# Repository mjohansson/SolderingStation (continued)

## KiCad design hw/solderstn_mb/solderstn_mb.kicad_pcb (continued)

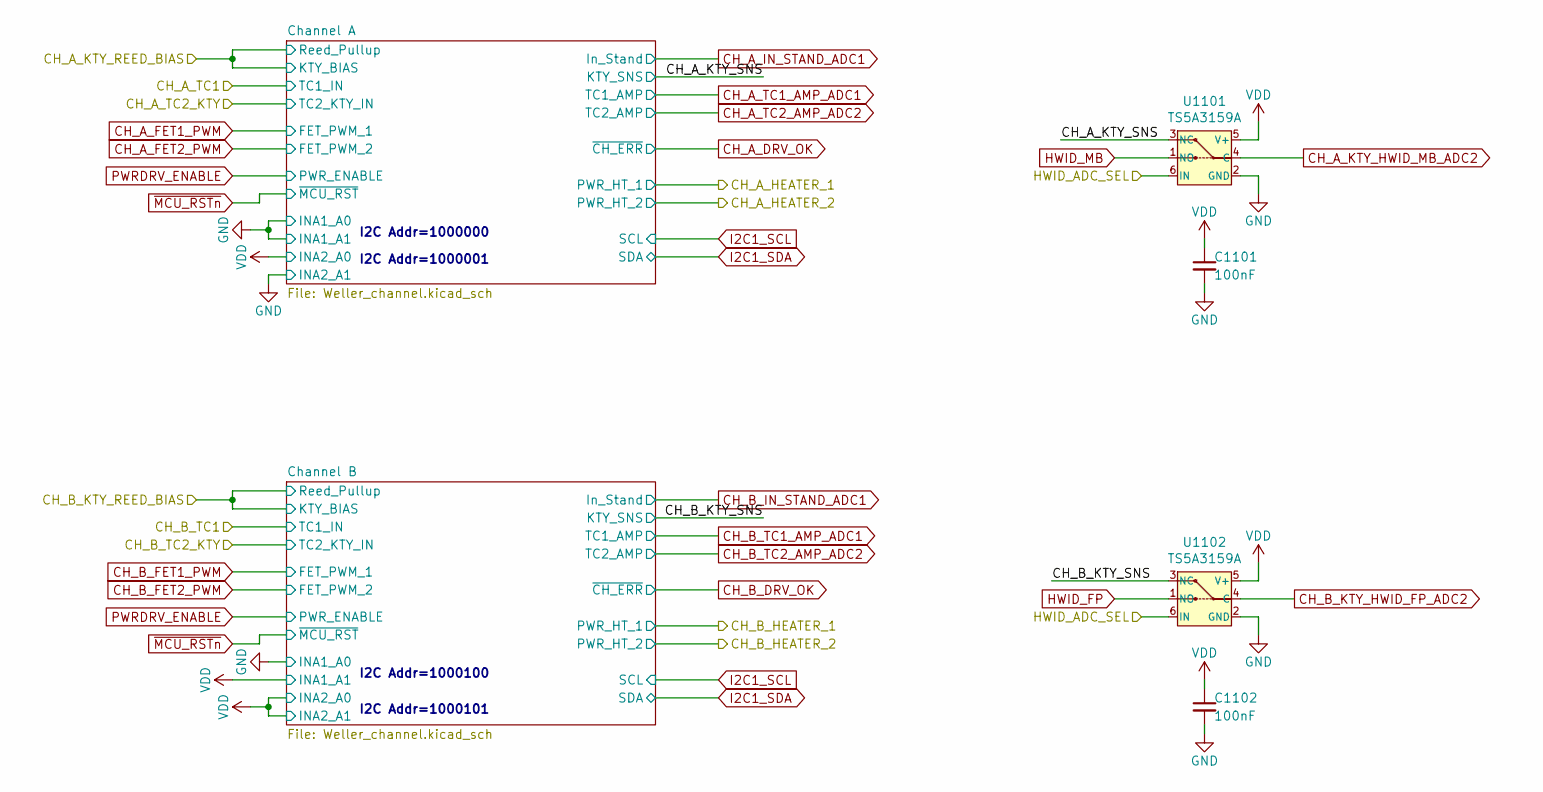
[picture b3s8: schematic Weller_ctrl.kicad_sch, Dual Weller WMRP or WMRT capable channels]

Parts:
C1101, C1102: 100nF; C_0402_1005Metric; JLC_part Basic
U1101, U1102: TS5A3159A; TSOT-23-6; JLC_part Extended

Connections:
/STM32F429 MCU/HWID_ADC_SELECT: U1101.6 (IN), U1102.6 (IN); also elsewhere on the board
/Weller contol/CH_A_KTY_SNS: U1101.3 (NC); also elsewhere on the board
/Weller contol/CH_B_KTY_SNS: U1102.3 (NC); also elsewhere on the board
AGND: C1101.2, C1102.2, U1101.2 (GND), U1102.2 (GND); also elsewhere on the board
CH_A_KTY_HWID_MB_ADC2: U1101.4 (C); also elsewhere on the board
CH_B_KTY_HWID_FP_ADC2: U1102.4 (C); also elsewhere on the board
HWID_FP: U1102.1 (NO); also elsewhere on the board
HWID_MB: U1101.1 (NO); also elsewhere on the board
VCC: C1101.1, C1102.1, U1101.5 (V+), U1102.5 (V+); also elsewhere on the board

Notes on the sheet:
I2C Addr=1000100
I2C Addr=1000001
I2C Addr=1000101
I2C Addr=1000000

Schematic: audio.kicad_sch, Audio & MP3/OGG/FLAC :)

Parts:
C1801, C1804, C1805, C1808: 2u2; C_0603_1608Metric; JLC_part Basic
C1802, C1806: 100nF; C_0402_1005Metric; JLC_part Basic
C1803, C1807: 470nF; C_0402_1005Metric; JLC_part Basic
J1801, J1803: CES-30207-158L120-67_Molex-PicoBlade_conn; Molex_PicoBlade_53398-0271_1x02-1MP_P1.25mm_Vertical
J1802, J1804: CES-703116-28PM_JST-conn; JST_PH_S2B-PH-SM4-TB_1x02-1MP_P2.00mm_Horizontal
JP1801, JP1802: dogbone_3_ud; db3_ud_0402
LS1801, LS1803: CES-30207-158L120-67; CUI_CES-30207
LS1802, LS1804: CES-703116-28PM; CUI_CES-703116-28PM
R1801, R1806: 15k; R_0402_1005Metric; JLC_part Basic
R1802, R1807: 1k5; R_0402_1005Metric; JLC_part Basic
R1803, R1809: 10k; R_0402_1005Metric; JLC_part Basic
R1804, R1810: 0R; R_1206_3216Metric; JLC_part Basic
R1805, R1808: DNM; R_0402_1005Metric
U1801, U1802: TS4990IDT; SOIC-8_3.9x4.9mm_P1.27mm

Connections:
/Audio & int. speakers/VLSI VS1063 DSP/codec/VS_L_out: C1807.2, R1808.1; also elsewhere on the board
/Audio & int. speakers/VLSI VS1063 DSP/codec/VS_R_out: C1803.2, R1805.2; also elsewhere on the board
/Rear panel connections/L_ch: U1802.8 (VOUT2); also elsewhere on the board
/Rear panel connections/L_int: R1810.1; also elsewhere on the board
/Rear panel connections/R_ch: U1801.8 (VOUT2); also elsewhere on the board
/Rear panel connections/R_int: R1804.1; also elsewhere on the board
AGND: C1801.1, C1802.1, C1804.1, C1805.1, C1806.1, C1808.1, R1805.1, R1808.2, U1801.7 (GND), U1802.7 (GND); also elsewhere on the board
unnamed: C1803.1, R1803.2
unnamed: C1804.2, U1801.2 (BYPASS), U1801.3 (Vin+)
unnamed: C1807.1, R1809.2
unnamed: C1808.2, U1802.2 (BYPASS), U1802.3 (Vin+)
unnamed: J1801.1 (+), J1802.1 (+), R1804.2
unnamed: J1801.2 (-), J1802.2 (-), R1802.1, U1801.5 (VOUT1)
unnamed: J1803.1 (+), J1804.1 (+), R1810.2
unnamed: J1803.2 (-), J1804.2 (-), R1807.1, U1802.5 (VOUT1)
unnamed: R1801.1, R1802.2
unnamed: R1801.2, R1803.1, U1801.4 (Vin-)
unnamed: R1806.1, R1807.2
unnamed: R1806.2, R1809.1, U1802.4 (Vin-)
VCC: JP1801.3, JP1802.3; also elsewhere on the board
VMAIN: C1801.2, C1802.2, C1805.2, C1806.2, JP1801.1, JP1801.2, JP1802.1, JP1802.2, U1801.6 (VCC), U1802.6 (VCC); also elsewhere on the board
~AUDIO_MUTEn: U1801.1 (~STBY), U1802.1 (~STBY); also elsewhere on the board

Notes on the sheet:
JST JST_PH_S2B-PH-SM4-TB for CES-703116
- +
F_AC [470n, 10k] = 34Hz
Using internal speakers until a 3.5mm plug is inserted; then switching to the external load. The switch is integrated in the headphone connector (rear panel)
A = Rf/Ri = 1,65 Vi = 3,0 * 1,65 -> Vo_max = 4,95
Right channel
Optional MP3/Ogg codec
Header for CES-30207 : Molex Picoblade 53398-0271
Left channel
Alternative interior enclosed speakers, CUI Devices CES-series; either 30x20x7mm or 70x31x16.5mm
Can encode MCU DAC-output to Ogg or MP3 (e.g. to record FM-radio data) Or decode MP3/Ogg/FLAC/etc compressed audio files, e.g. from USB storage or network streams
Molex Picoblade 53398-0271 for CES-30207

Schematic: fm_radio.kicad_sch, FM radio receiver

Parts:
C2201: 100nF; C_0402_1005Metric; JLC_part Basic
C2202: 10nF; C_0402_1005Metric; JLC_part Basic
C2203: 10pF; C_0402_1005Metric; JLC_part Basic
C2204: 470nF; C_0402_1005Metric; JLC_part Basic
C2205: 470pF; C_0402_1005Metric; JLC_part Basic
D2201, D2202: CM1213A-01SO; SOT-23
J801, J2204: alt-placement; SMA_Molex_73251-2200_Horizontal
J2201: Conn_01x02; PinHeader_1x02_P2.54mm_Vertical
J2202: Molex_PicoBlade-53398-0271; Molex_PicoBlade_53398-0271_1x02-1MP_P1.25mm_Vertical
J2203: Conn_Coaxial; SMA_Molex_73251-2200_Horizontal
JP2201: dogbone_3_ud; db3_ud_0402
JP2202, JP2203, JP2204: dogbone_2_ud; db2_ud_0402
L2201: 220nH; L_0603_1608Metric; JLC_part Extended
R2201: 560R; R_0603_1608Metric; JLC_part Basic
R2202, R2203: 1k; R_0402_1005Metric; JLC_part Basic
U2201: Si4735-D60-GU; SSOP-24_3.9x8.7mm_P0.635mm

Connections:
/FM-radio rx/FMI: C2205.1, D2202.1 (CH1), J2202.1, JP2203.1, JP2203.2, JP2204.1
AGND: C2201.2, C2203.1, D2201.2 (VP), D2201.3 (VN), D2202.2 (VP), D2202.3 (VN), J2201.2, J2202.2, J2203.2 (Ext), JP2201.1, JP2201.2, JP2202.1, JP2202.2, L2201.2, U2201.9 (RFGND), U2201.13 (GND), U2201.14 (GND), U2201.16 (~SEN); also elsewhere on the board
AVDD: C2202.1, U2201.21 (VA); also elsewhere on the board
FM_I2S_CK: R2203.1; also elsewhere on the board
FM_I2S_SD: R2201.1; also elsewhere on the board
FM_I2S_WS: C2203.2, R2202.1; also elsewhere on the board
I2C1_SCL: U2201.17 (SCLK); also elsewhere on the board
I2C1_SDA: U2201.18 (SDIO); also elsewhere on the board
unnamed: C2202.2, U2201.22 (DBYP)
unnamed: C2204.1, D2201.1 (CH1), J2201.1
unnamed: C2204.2, U2201.12 (AMI)
unnamed: C2205.2, L2201.1, U2201.8 (FMI)
unnamed: J2203.1 (In), JP2204.2
unnamed: R2201.2, U2201.1 (DOUT)
unnamed: R2202.2, U2201.2 (DFS)
unnamed: R2203.2, U2201.3 (GPO3/[DCLK])
RCLKo_8M: U2201.19 (RCLK); also elsewhere on the board
VCC: C2201.1, JP2201.3, U2201.20 (VD); also elsewhere on the board
~FM_INTn: U2201.4 (GPO2/[~INT]); also elsewhere on the board
~SYS_RSTn: U2201.15 (~RST); also elsewhere on the board

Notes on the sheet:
To ferrite loop stick, apprx 180-450µH
(was: 56nH / LQW18AN56NJ00D)
~{SEN} = 0 : I2C addr=0010001 ~{SEN} = 1 : I2C addr=1100011
(OTS cable assm: e.g. 151340203)
To e.g. 1/4 FM wire- or screw telescope (whip) antenna

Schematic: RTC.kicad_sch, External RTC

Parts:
C2101, C2102, C2103: 100nF; C_0402_1005Metric; JLC_part Basic
Q2101: AO3401A; SOT-23; JLC_part Basic
Q2102: DMG1013T; SOT-523_handsoldering; JLC_part Extended
R2102: 10k; R_0402_1005Metric; JLC_part Basic
RN2101: 4x10k_0402; R_Array_Convex_4x0402; JLC_part Basic
RTC2101: DS3231_Module_6pins; DS3231_module_6pin_horizontal_mnt
U2101: DS3231M; SOIC-16W_7.5x10.3mm_P1.27mm; JLC_part Basic
U2102: AT24C256C-SSHL-T; SO-8_3.9x4.9mm_P1.27mm; JLC_part Basic
U2103: DS3231MZ; SOIC-8_3.9x4.9mm_P1.27mm; JLC_part Extended

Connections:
+BATT: U2101.14 (VBAT), U2103.6 (VBAT)
/STM32F429 MCU/32kHz: RTC2101.1 (32K), U2101.1 (32KHZ), U2103.1 (32KHZ); also elsewhere on the board
/STM32F429 MCU/External RTC/PG: Q2101.1 (G), Q2102.1 (G), U2101.4 (~RST), U2103.4 (~RST)
/STM32F429 MCU/External RTC/~WEn: Q2101.3 (D), Q2102.3 (D), RN2101.5 (R4.2), U2102.7 (WP)
/STM32F429 MCU/~RTC_INTn: R2102.2, RTC2101.2 (~INT/SQW), U2101.3 (~INT/SQW), U2103.3 (~INT/SQW); also elsewhere on the board
AGND: C2101.1, C2102.1, C2103.1, RN2101.4 (R4.1), RTC2101.6 (GND), U2101.5 (GND), U2101.6 (GND), U2101.7 (GND), U2101.8 (GND), U2101.9 (GND), U2101.10 (GND), U2101.11 (GND), U2101.12 (GND), U2101.13 (GND), U2102.4 (GND), U2103.5 (GND); also elsewhere on the board
I2C1_SCL: RTC2101.3 (SCL), U2101.16 (SCL), U2102.6 (SCL), U2103.8 (SCL); also elsewhere on the board
I2C1_SDA: RTC2101.4 (SDA), U2101.15 (SDA), U2102.5 (SDA), U2103.7 (SDA); also elsewhere on the board
unnamed: RN2101.6 (R3.2), U2102.3 (A2)
unnamed: RN2101.7 (R2.2), U2102.2 (A1)
unnamed: RN2101.8 (R1.2), U2102.1 (A0)
VCC: C2101.2, C2102.2, C2103.2, Q2101.2 (S), Q2102.2 (S), R2102.1, RN2101.1 (R1.1), RN2101.2 (R2.1), RN2101.3 (R3.1), RTC2101.5 (VCC), U2101.2 (VCC), U2102.8 (VCC), U2103.2 (VCC); also elsewhere on the board

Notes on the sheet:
EEPROM write-protection on power-loss: ~{RES}/PG pin high when VDD > 2.7V(max), open-drain low when VDD < ~{2.5V(typ}). Do not pull-up, internal ~{50K} in DS3231.
DS3231 RTC module
Alt. fp : Mount either -M or -MZ Place SOIC-8 footprint overlapping the pins 1-4/13-16 of SOIC-16
TODO: Remove all on-board RTC & EEPROM, use just RTC-module
DS3132 I2C address : b1101000<R~{w}>
Alternative footprint : Mount Q2101 or Q2102 but not both. footprint SC-523 can be placed overlapping the SOT-23
EEPROM I2C address : b1010<A2..A0><R/~{w}> = b1010111<R~{w}>

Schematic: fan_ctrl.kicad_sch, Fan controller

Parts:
C601: 10uF/16V; C_0805_2012Metric; JLC_part Basic
C602: 100nF; C_0402_1005Metric; JLC_part Basic
JP601: dogbone_3_ud; db3_ud_0402
M601: Fan_4pin; FanPinHeader_1x04_P2.54mm_Vertical; Mfg_pn Molex 47053-1000
Q601: DMG1012T; SOT-523_handsoldering; JLC_part Extended
R601: 12k; R_0402_1005Metric; JLC_part Basic
R602, R603: 10k; R_0402_1005Metric; JLC_part Basic
U601: 74LVC2G17gw; SOT-363_SC-70-6_Handsoldering; JLC_part Extended

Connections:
AGND: C601.1, C602.1, M601.1 (-), Q601.2 (S), R602.1, R603.1, U601.2 (GND), U601.3; also elsewhere on the board
FAN1_PWM: Q601.1 (G), R603.2; also elsewhere on the board
FAN1_RPM: U601.6; also elsewhere on the board
unnamed: M601.3 (Tacho), R601.1, R602.2, U601.1
unnamed: M601.4 (PWM), Q601.3 (D)
VCC: C602.2, U601.5 (VCC); also elsewhere on the board
VIN: JP601.3; also elsewhere on the board
VMAIN: C601.2, JP601.1, JP601.2, M601.2 (+), R601.2; also elsewhere on the board

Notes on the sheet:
Fan pin3 (Tacho) is open-drain, 2 pulses/revolution. The voltage divider should ensure that the inactive (high) level is between 2.2 .. 5.5V for the Schmitt buffer input, regardless of 12V or 5V fan
Fan pin4 (PWM) supplies pull-up resistor in fan hub (max 5.5V)
(12V fan)
(5V fan)

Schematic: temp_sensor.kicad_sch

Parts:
C701: 100nF; C_0402_1005Metric; JLC_part Basic
U701: TMP100; TSOT-23-6; JLC_part Extended

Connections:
/Front panel connections/Temp.sensor 1/A0: U701.5 (ADD0)
AGND: C701.2, U701.2 (GND); also elsewhere on the board
GND: U701.3 (ADD1); also elsewhere on the board
I2C1_SCL: U701.1 (SCL); also elsewhere on the board
I2C1_SDA: U701.6 (SDA); also elsewhere on the board
VCC: C701.1, U701.4 (V+); also elsewhere on the board

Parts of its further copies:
C801, C901: 100nF; C_0402_1005Metric; JLC_part Basic
U801, U901: TMP100; TSOT-23-6; JLC_part Extended

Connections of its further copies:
/Front panel connections/Temp.sensor 2/A1: U801.3 (ADD1)
/Front panel connections/Temp.sensor 3/A1: U901.3 (ADD1)
AGND: C801.2, C901.2, U801.2 (GND), U901.2 (GND); also elsewhere on the board
GND: U801.5 (ADD0); also elsewhere on the board
I2C1_SCL: U801.1 (SCL), U901.1 (SCL); also elsewhere on the board
I2C1_SDA: U801.6 (SDA), U901.6 (SDA); also elsewhere on the board
VCC: C801.1, C901.1, U801.4 (V+), U901.4 (V+), U901.5 (ADD0); also elsewhere on the board

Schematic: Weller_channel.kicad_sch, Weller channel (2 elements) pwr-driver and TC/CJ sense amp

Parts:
C1201, C1202, C1205, C1207: 10nF; C_0402_1005Metric; JLC_part Basic
C1203, C1208: 1uF; C_0402_1005Metric; JLC_part Basic
C1204, C1206, C1209, C1210, C1211: 100nF; C_0402_1005Metric; JLC_part Basic
R1201, R1202, R1204, R1206, R1211, R1214, R1216: 1k; R_0402_1005Metric; JLC_part Basic
R1203, R1208, R1209, R1210, R1218, R1219, R1220, R1221, R1222: 10k; R_0402_1005Metric; JLC_part Basic
R1205, R1212: 10mR; R_1206_3216Metric; JLC_part Extended
R1207, R1217: 330k; R_0402_1005Metric; JLC_part Basic
R1213, R1215: 5k6; R_0402_1005Metric; JLC_part Basic
U1201: AD8552ARU; TSSOP-8_4.4x3mm_P0.65mm; JLC_part Extended
U1202, U1204: INA226; VSSOP-10_3x3mm_P0.5mm; JLC_part Extended
U1203: TPS2HB16AQ1; HTSSOP-16-1EP_4.4x5mm_P0.65mm_EP3.4x5mm_Mask3x3mm_ThermalVi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
U1205, U1206, U1207: 74LVC1G11dck; SOT-363_SC-70-6_Handsoldering

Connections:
+12V: C1202.2, C1203.2, R1213.1, R1215.2, U1202.8 (Vbus), U1203.17 (VBB), U1204.8 (Vbus); also elsewhere on the board
/Rear panel connections/CH_A_TC1: R1201.2, R1202.2, R1204.1; also elsewhere on the board
/STM32F429 PWR/KTY_REED_BIAS_CH_A: R1201.1, R1211.1; also elsewhere on the board
/Weller contol/CH_A_KTY_SNS: R1211.2, R1214.2; also elsewhere on the board
/Weller contol/Channel A/HEATER_1: R1205.1, U1202.10 (Vin+); also elsewhere on the board
/Weller contol/Channel A/HEATER_2: R1212.1, U1204.10 (Vin+); also elsewhere on the board
/Weller contol/Channel A/HT1_EN: U1203.4 (EN1), U1205.4
/Weller contol/Channel A/HT2_EN: U1203.13 (EN2), U1206.4
/Weller contol/Channel A/PWM_OK_1: U1205.3, U1207.6; also elsewhere on the board
/Weller contol/Channel A/PWM_OK_2: U1206.3, U1207.3; also elsewhere on the board
/Weller contol/Channel A/Vout1: C1204.2, R1205.2, U1202.9 (Vin-), U1203.6 (VOUT1), U1203.7 (VOUT1), U1203.8 (VOUT1)
/Weller contol/Channel A/Vout2: C1206.2, R1212.2, U1203.9 (VOUT2), U1203.10 (VOUT2), U1203.11 (VOUT2), U1204.9 (Vin-)
/Weller contol/Channel A/~OC_ERR_1: R1203.2, U1202.3 (~Alert); also elsewhere on the board
/Weller contol/Channel A/~OC_ERR_2: R1219.2, U1204.3 (~Alert); also elsewhere on the board
AGND: C1201.2, C1202.1, C1203.1, C1204.1, C1205.2, C1206.1, C1207.1, C1208.1, C1209.1, C1210.1, C1211.1, R1206.2, R1208.2, R1209.2, R1210.2, R1216.2, R1218.2, R1220.2, R1221.2, R1222.2, U1201.4 (V-), U1202.7 (GND), U1203.1 (GND), U1204.7 (GND), U1205.2 (GND), U1206.2 (GND), U1207.2 (GND); also elsewhere on the board
AVDD: C1207.2, C1208.2, U1201.8 (V+); also elsewhere on the board
CH_A_DRV_OK: U1207.4; also elsewhere on the board
CH_A_FET1_PWM: R1220.1, U1205.6; also elsewhere on the board
CH_A_FET2_PWM: R1221.1, U1206.6; also elsewhere on the board
CH_A_IN_STAND_ADC1: R1204.2; also elsewhere on the board
CH_A_TC1_AMP_ADC1: R1207.1, U1201.1; also elsewhere on the board
CH_A_TC2_AMP_ADC2: R1217.1, U1201.7; also elsewhere on the board
GND: U1202.1 (A1), U1202.2 (A0), U1204.1 (A1); also elsewhere on the board
I2C1_SCL: U1202.5 (SCL), U1204.5 (SCL); also elsewhere on the board
I2C1_SDA: U1202.4 (SDA), U1204.4 (SDA); also elsewhere on the board
unnamed: R1202.1, U1201.3 (+)
unnamed: R1206.1, R1207.2, U1201.2 (-)
unnamed: R1208.1, U1203.16 (DIA_EN)
unnamed: R1209.1, U1203.14 (SEL1)
unnamed: R1210.1, U1203.15 (SEL2)
unnamed: R1213.2, U1203.5 (ILIM1)
unnamed: R1214.1, U1201.5 (+)
unnamed: R1215.1, U1203.12 (ILIM2)
unnamed: R1216.1, R1217.2, U1201.6 (-)
unnamed: R1218.1, U1203.2 (SNS)
PWRDRV_ENABLE: R1222.1, U1203.3 (LATCH), U1205.1, U1206.1; also elsewhere on the board
VCC: C1201.1, C1205.1, C1209.2, C1210.2, C1211.2, R1203.1, R1219.1, U1202.6 (VS), U1204.6 (VS), U1205.5 (VCC), U1206.5 (VCC), U1207.1, U1207.5 (VCC); also elsewhere on the board
VDD: U1204.2 (A0); also elsewhere on the board

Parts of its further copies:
C1501, C1502, C1505, C1507: 10nF; C_0402_1005Metric; JLC_part Basic
C1503, C1508: 1uF; C_0402_1005Metric; JLC_part Basic
C1504, C1506, C1509, C1510, C1511: 100nF; C_0402_1005Metric; JLC_part Basic
R1501, R1502, R1504, R1506, R1511, R1514, R1516: 1k; R_0402_1005Metric; JLC_part Basic
R1503, R1508, R1509, R1510, R1518, R1519, R1520, R1521, R1522: 10k; R_0402_1005Metric; JLC_part Basic
R1505, R1512: 10mR; R_1206_3216Metric; JLC_part Extended
R1507, R1517: 330k; R_0402_1005Metric; JLC_part Basic
R1513, R1515: 5k6; R_0402_1005Metric; JLC_part Basic
U1501: AD8552ARU; TSSOP-8_4.4x3mm_P0.65mm; JLC_part Extended
U1502, U1504: INA226; VSSOP-10_3x3mm_P0.5mm; JLC_part Extended
U1503: TPS2HB16AQ1; HTSSOP-16-1EP_4.4x5mm_P0.65mm_EP3.4x5mm_Mask3x3mm_ThermalVi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
U1505, U1506, U1507: 74LVC1G11dck; SOT-363_SC-70-6_Handsoldering

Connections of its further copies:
+12V: C1502.2, C1503.2, R1513.1, R1515.2, U1502.8 (Vbus), U1503.17 (VBB), U1504.8 (Vbus); also elsewhere on the board
/Rear panel connections/CH_B_TC1: R1501.2, R1502.2, R1504.1; also elsewhere on the board
/STM32F429 PWR/KTY_REED_BIAS_CH_B: R1501.1, R1511.1; also elsewhere on the board
/Weller contol/CH_B_KTY_SNS: R1511.2, R1514.2; also elsewhere on the board
/Weller contol/Channel B/HEATER_1: R1505.1, U1502.10 (Vin+); also elsewhere on the board
/Weller contol/Channel B/HEATER_2: R1512.1, U1504.10 (Vin+); also elsewhere on the board
/Weller contol/Channel B/HT1_EN: U1503.4 (EN1), U1505.4
/Weller contol/Channel B/HT2_EN: U1503.13 (EN2), U1506.4
/Weller contol/Channel B/PWM_OK_1: U1505.3, U1507.6; also elsewhere on the board
/Weller contol/Channel B/PWM_OK_2: U1506.3, U1507.3; also elsewhere on the board
/Weller contol/Channel B/Vout1: C1504.2, R1505.2, U1502.9 (Vin-), U1503.6 (VOUT1), U1503.7 (VOUT1), U1503.8 (VOUT1)
/Weller contol/Channel B/Vout2: C1506.2, R1512.2, U1503.9 (VOUT2), U1503.10 (VOUT2), U1503.11 (VOUT2), U1504.9 (Vin-)
/Weller contol/Channel B/~OC_ERR_1: R1503.2, U1502.3 (~Alert); also elsewhere on the board
/Weller contol/Channel B/~OC_ERR_2: R1519.2, U1504.3 (~Alert); also elsewhere on the board
AGND: C1501.2, C1502.1, C1503.1, C1504.1, C1505.2, C1506.1, C1507.1, C1508.1, C1509.1, C1510.1, C1511.1, R1506.2, R1508.2, R1509.2, R1510.2, R1516.2, R1518.2, R1520.2, R1521.2, R1522.2, U1501.4 (V-), U1502.7 (GND), U1503.1 (GND), U1504.7 (GND), U1505.2 (GND), U1506.2 (GND), U1507.2 (GND); also elsewhere on the board
AVDD: C1507.2, C1508.2, U1501.8 (V+); also elsewhere on the board
CH_B_DRV_OK: U1507.4; also elsewhere on the board
CH_B_FET1_PWM: R1520.1, U1505.6; also elsewhere on the board
CH_B_FET2_PWM: R1521.1, U1506.6; also elsewhere on the board
CH_B_IN_STAND_ADC1: R1504.2; also elsewhere on the board
CH_B_TC1_AMP_ADC1: R1507.1, U1501.1; also elsewhere on the board
CH_B_TC2_AMP_ADC2: R1517.1, U1501.7; also elsewhere on the board
GND: U1502.2 (A0); also elsewhere on the board
I2C1_SCL: U1502.5 (SCL), U1504.5 (SCL); also elsewhere on the board
I2C1_SDA: U1502.4 (SDA), U1504.4 (SDA); also elsewhere on the board
unnamed: R1502.1, U1501.3 (+)
unnamed: R1506.1, R1507.2, U1501.2 (-)
unnamed: R1508.1, U1503.16 (DIA_EN)
unnamed: R1509.1, U1503.14 (SEL1)
unnamed: R1510.1, U1503.15 (SEL2)
unnamed: R1513.2, U1503.5 (ILIM1)
unnamed: R1514.1, U1501.5 (+)
unnamed: R1515.1, U1503.12 (ILIM2)
unnamed: R1516.1, R1517.2, U1501.6 (-)
unnamed: R1518.1, U1503.2 (SNS)
PWRDRV_ENABLE: R1522.1, U1503.3 (LATCH), U1505.1, U1506.1; also elsewhere on the board
VCC: C1501.1, C1505.1, C1509.2, C1510.2, C1511.2, R1503.1, R1519.1, U1502.6 (VS), U1504.6 (VS), U1505.5 (VCC), U1506.5 (VCC), U1507.1, U1507.5 (VCC); also elsewhere on the board
VDD: U1502.1 (A1), U1504.1 (A1), U1504.2 (A0); also elsewhere on the board

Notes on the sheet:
Gain = 331 : TC voltage 7.55mv -> 2.5V For a D-type thermocouple, 7.55mv corresponds to approx. +470 C WITHOUT cold-junction compensation; or +490 C with CJC for +30C Conclusion: for the normal working range of [25 .. 450] C, a gain of 330(+1) is suitable for a Vref of 2.5V (See https://pypi.org/pr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
A higher than expected V_TC and/or unfavorable tolerances or offset errors etc could reault in an amplified voltage > Vref (2.5V), since VDDA is 3.0V. However, the STM32 ADC tolerates input signals > Vref. It will of course clip at max-code, but it's electrically safe

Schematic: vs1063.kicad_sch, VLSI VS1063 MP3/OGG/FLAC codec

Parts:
C1901, C1902: 2u2; C_0603_1608Metric; JLC_part Basic
C1903, C1908, C1912: 10uF; C_0402_1005Metric; JLC_part Basic
C1904, C1905, C1906, C1907, C1909, C1910, C1911, C1913, C1914, C1915, C1916, C1923: 100nF; C_0402_1005Metric; JLC_part Basic
C1917, C1928: 3n3; C_0402_1005Metric; JLC_part Basic
C1918, C1921: 10pF; C_0402_1005Metric; JLC_part Basic
C1919, C1920, C1926, C1927: 10nF; C_0402_1005Metric; JLC_part Basic
C1922: 47nF; C_0603_1608Metric; JLC_part Basic
C1924, C1925: 1uF; C_1206_3216Metric; JLC_part Basic
C1929: 1uF; C_0402_1005Metric; JLC_part Basic
R1901, R1909: DNM; R_0402_1005Metric
R1902, R1910, R1911, R1912: 470R; R_0402_1005Metric; JLC_part Basic
R1903, R1904, R1913, R1914, R1915: 10k; R_0402_1005Metric; JLC_part Basic
R1905, R1906: 22R; R_0402_1005Metric; JLC_part Basic
R1907: 1M; R_0402_1005Metric; JLC_part Basic
R1908: 10R; R_0402_1005Metric; JLC_part Basic
TP1901, TP1902: TP; TP_SMD_1.2c
U1901: MIC5365-1.8YD5; SOT-23-5
U1902, U1904: TS5A3159A; SOT-23-6; JLC_part Extended
U1903: VS1063a; LQFP-48_7x7mm_P0.5mm
Y1901: 12.288M; Crystal_SMD_SeikoEpson_TSX3225-4Pin_3.2x2.5mm; JLC_part Extended

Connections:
+1V8: C1902.1, C1903.1, C1904.1, C1905.1, C1906.1, C1907.1, U1901.5 (VOUT), U1903.5 (CVDD), U1903.7 (CVDD), U1903.24 (CVDD), U1903.31 (CVDD)
/Audio & int. speakers/VLSI VS1063 DSP/codec/Lout: R1905.2, U1902.3 (NC), U1903.46 (LEFT)
/Audio & int. speakers/VLSI VS1063 DSP/codec/Rout: R1906.2, U1903.39 (RIGHT), U1904.3 (NC)
/Audio & int. speakers/VLSI VS1063 DSP/codec/VS_L_out: C1917.1, R1902.1; also elsewhere on the board
/Audio & int. speakers/VLSI VS1063 DSP/codec/VS_R_out: C1928.1, R1912.1; also elsewhere on the board
AGND: C1901.2, C1902.2, C1903.2, C1904.2, C1905.2, C1906.2, C1907.2, C1908.2, C1909.2, C1910.2, C1911.2, C1912.2, C1913.2, C1914.2, C1915.2, C1916.2, C1917.2, C1918.1, C1919.2, C1920.2, C1921.1, C1922.2, C1923.2, C1926.1, C1927.2, C1928.2, C1929.2, R1913.2, R1914.2, R1915.2, U1901.2 (GND), U1902.2 (GND), U1903.4 (DGND), U1903.16 (DGND), U1903.20 (DGND), U1903.21 (DGND), U1903.22 (DGND), U1903.35 (DGND), U1903.37 (AGND), U1903.40 (AGND), U1903.41 (AGND), U1903.47 (AGND), U1904.2 (GND), Y1901.2, Y1901.4; also elsewhere on the board
AUDIO_PATH_SEL: U1902.6 (IN), U1904.6 (IN); also elsewhere on the board
AVDD: C1912.1, C1913.1, C1914.1, C1915.1, C1916.1, C1923.1, U1902.5 (V+), U1903.38 (AVDD), U1903.43 (AVDD), U1903.45 (AVDD), U1904.5 (V+); also elsewhere on the board
DAC_OUT1: C1924.1, R1901.2, U1902.1 (NO); also elsewhere on the board
DAC_OUT2: C1925.1, R1909.2, U1904.1 (NO); also elsewhere on the board
IOVDD: C1901.1, C1908.1, C1909.1, C1910.1, C1911.1, R1903.2, R1904.1, U1901.1 (VIN), U1901.3 (EN), U1903.6 (IOVDD), U1903.14 (IOVDD), U1903.19 (IOVDD), U1903.32 (~TESTn)
unnamed: C1918.2, R1907.1, U1903.18 (XTI/MCLK), Y1901.1
unnamed: C1919.1, R1905.1
unnamed: C1920.1, R1906.1
unnamed: C1921.2, R1907.2, U1903.17 (XTO), Y1901.3
unnamed: C1922.1, R1908.1
unnamed: C1924.2, R1910.1
unnamed: C1925.2, R1911.1
unnamed: C1926.2, R1910.2, U1903.1 (MICP/LINEINL)
unnamed: C1927.1, R1911.2, U1903.48 (LINEINR)
unnamed: C1929.1, U1903.44 (RCAP)
unnamed: R1901.1, R1902.2, U1902.4 (C)
unnamed: R1903.1, U1903.13 (~DCSn/BSYNC)
unnamed: R1904.2, TP1901.1, U1903.26 (RX)
unnamed: R1908.2, U1903.42 (GBUF)
unnamed: R1909.1, R1912.2, U1904.4 (C)
unnamed: R1913.1, U1903.9 (GPIO2/DCLK), U1903.10 (GPIO3/SDATA), U1903.11 (GPIO6/I2S_SCK), U1903.12 (GPIO7/I2S_SD)
unnamed: R1914.1, U1903.33 (GPIO0), U1903.34 (GPIO1), U1903.36 (GPIO4/I2S_LR)
unnamed: R1915.1, U1903.25 (GPIO5/I2S_MCK)
unnamed: TP1902.1, U1903.27 (TX)
VS1063_DREQ: U1903.8 (DREQ); also elsewhere on the board
VS1063_MISO: U1903.30 (SO); also elsewhere on the board
VS1063_MOSI: U1903.29 (SI); also elsewhere on the board
VS1063_SCK: U1903.28 (SCLK); also elsewhere on the board
~SYS_RSTn: U1903.3 (~RESETn); also elsewhere on the board
~VS1063_CSn: U1903.23 (~CSn); also elsewhere on the board

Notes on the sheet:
F_LP [470, 3n3] = 100kHz
Audio-path bypass (eg if VS1063 n/m)
Audio source selection 0 : MCU DAC 1 : VS1053 DAC

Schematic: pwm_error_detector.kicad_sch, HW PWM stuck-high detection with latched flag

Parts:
C1301, C1303, C1304, C1305: 100nF; C_0402_1005Metric; JLC_part Basic
C1302: 1uF; C_0402_1005Metric; JLC_part Basic
D1301: Red; LED_0603_1608Metric; JLC_part Basic
Q1301: DMG1013T; SOT-523_handsoldering; JLC_part Extended
R1301, R1302: 15k; R_0402_1005Metric; JLC_part Basic
R1303: 10k; R_0402_1005Metric; JLC_part Basic
R1304: 1k; R_0402_1005Metric; JLC_part Basic
U1301: NE556d; SOIC-14_3.9x8.7mm_P1.27mm; JLC_part Extended
U1302: 74LVC1G175dck; SOT-363_SC-70-6_Handsoldering; JLC_part Extended
U1303: 74LVC1G11dck; SOT-363_SC-70-6_Handsoldering

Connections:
/Weller contol/Channel A/HEATER_1: R1301.1; also elsewhere on the board
/Weller contol/Channel A/PWM error detector 1/~CLR_FLAG: U1302.6 (~CLR), U1303.4
/Weller contol/Channel A/PWM error detector 1/~PULSE_ERR: U1301.5 (Q), U1303.6
/Weller contol/Channel A/PWM error detector 1/~PULSEn_D: Q1301.1 (G), R1301.2, R1303.1, U1301.6 (TR)
/Weller contol/Channel A/PWM error detector 2/~PULSE_ERR: U1301.9 (Q); also elsewhere on the board
/Weller contol/Channel A/PWM error detector 2/~PULSEn_D: U1301.8 (TR); also elsewhere on the board
/Weller contol/Channel A/PWM_OK_1: D1301.1 (K), U1302.4 (Q); also elsewhere on the board
/Weller contol/Channel A/~OC_ERR_1: U1303.1; also elsewhere on the board
AGND: C1301.2, C1302.2, C1303.2, C1304.2, C1305.2, Q1301.3 (D), R1303.2, U1301.7 (GND), U1302.2 (GND), U1303.2 (GND); also elsewhere on the board
unnamed: C1301.1, U1301.3 (CV)
unnamed: C1302.1, Q1301.2 (S), R1302.2, U1301.1 (DIS), U1301.2 (THR)
unnamed 144: U1301.11 (CV); also elsewhere on the board
unnamed 145: U1301.12 (THR), U1301.13 (DIS); also elsewhere on the board
unnamed: D1301.2 (A), R1304.2
PWRDRV_ENABLE: U1302.1 (C); also elsewhere on the board
VCC: C1304.1, C1305.1, R1304.1, U1302.3 (D), U1302.5 (VCC), U1303.5 (VCC); also elsewhere on the board
VMAIN: C1303.1, R1302.1, U1301.4 (R), U1301.10 (R), U1301.14 (VCC); also elsewhere on the board
~MCU_RSTn: U1303.3; also elsewhere on the board

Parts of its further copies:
C1401, C1403, C1404, C1405, C1601, C1603, C1604, C1605, C1701, C1703, C1704, C1705: 100nF; C_0402_1005Metric; JLC_part Basic
C1402, C1602, C1702: 1uF; C_0402_1005Metric; JLC_part Basic
D1401, D1601, D1701: Red; LED_0603_1608Metric; JLC_part Basic
Q1401, Q1601, Q1701: DMG1013T; SOT-523_handsoldering; JLC_part Extended
R1401, R1402, R1601, R1602, R1701, R1702: 15k; R_0402_1005Metric; JLC_part Basic
R1403, R1603, R1703: 10k; R_0402_1005Metric; JLC_part Basic
R1404, R1604, R1704: 1k; R_0402_1005Metric; JLC_part Basic
U1401, U1602, U1701: 74LVC1G175dck; SOT-363_SC-70-6_Handsoldering; JLC_part Extended
U1402, U1603, U1702: 74LVC1G11dck; SOT-363_SC-70-6_Handsoldering
U1601: NE556d; SOIC-14_3.9x8.7mm_P1.27mm; JLC_part Extended

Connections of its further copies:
/Weller contol/Channel A/HEATER_2: R1401.1; also elsewhere on the board
/Weller contol/Channel A/PWM error detector 2/~CLR_FLAG: U1401.6 (~CLR), U1402.4
/Weller contol/Channel A/PWM error detector 2/~PULSE_ERR: U1402.6; also elsewhere on the board
/Weller contol/Channel A/PWM error detector 2/~PULSEn_D: Q1401.1 (G), R1401.2, R1403.1; also elsewhere on the board
/Weller contol/Channel A/PWM_OK_2: D1401.1 (K), U1401.4 (Q); also elsewhere on the board
/Weller contol/Channel A/~OC_ERR_2: U1402.1; also elsewhere on the board
/Weller contol/Channel B/HEATER_1: R1601.1; also elsewhere on the board
/Weller contol/Channel B/HEATER_2: R1701.1; also elsewhere on the board
/Weller contol/Channel B/PWM error detector 1/~CLR_FLAG: U1602.6 (~CLR), U1603.4
/Weller contol/Channel B/PWM error detector 1/~PULSE_ERR: U1601.5 (Q), U1603.6
/Weller contol/Channel B/PWM error detector 1/~PULSEn_D: Q1601.1 (G), R1601.2, R1603.1, U1601.6 (TR)
/Weller contol/Channel B/PWM error detector 2/~CLR_FLAG: U1701.6 (~CLR), U1702.4
/Weller contol/Channel B/PWM error detector 2/~PULSE_ERR: U1601.9 (Q), U1702.6
/Weller contol/Channel B/PWM error detector 2/~PULSEn_D: Q1701.1 (G), R1701.2, R1703.1, U1601.8 (TR)
/Weller contol/Channel B/PWM_OK_1: D1601.1 (K), U1602.4 (Q); also elsewhere on the board
/Weller contol/Channel B/PWM_OK_2: D1701.1 (K), U1701.4 (Q); also elsewhere on the board
/Weller contol/Channel B/~OC_ERR_1: U1603.1; also elsewhere on the board
/Weller contol/Channel B/~OC_ERR_2: U1702.1; also elsewhere on the board
AGND: C1401.2, C1402.2, C1403.2, C1404.2, C1405.2, C1601.2, C1602.2, C1603.2, C1604.2, C1605.2, C1701.2, C1702.2, C1703.2, C1704.2, C1705.2, Q1401.3 (D), Q1601.3 (D), Q1701.3 (D), R1403.2, R1603.2, R1703.2, U1401.2 (GND), U1402.2 (GND), U1601.7 (GND), U1602.2 (GND), U1603.2 (GND), U1701.2 (GND), U1702.2 (GND); also elsewhere on the board
unnamed 144: C1401.1; also elsewhere on the board
unnamed 145: C1402.1, Q1401.2 (S), R1402.2; also elsewhere on the board
unnamed: C1601.1, U1601.3 (CV)
unnamed: C1602.1, Q1601.2 (S), R1602.2, U1601.1 (DIS), U1601.2 (THR)
unnamed: C1701.1, U1601.11 (CV)
unnamed: C1702.1, Q1701.2 (S), R1702.2, U1601.12 (THR), U1601.13 (DIS)
unnamed: D1401.2 (A), R1404.2
unnamed: D1601.2 (A), R1604.2
unnamed: D1701.2 (A), R1704.2
PWRDRV_ENABLE: U1401.1 (C), U1602.1 (C), U1701.1 (C); also elsewhere on the board
VCC: C1404.1, C1405.1, C1604.1, C1605.1, C1704.1, C1705.1, R1404.1, R1604.1, R1704.1, U1401.3 (D), U1401.5 (VCC), U1402.5 (VCC), U1602.3 (D), U1602.5 (VCC), U1603.5 (VCC), U1701.3 (D), U1701.5 (VCC), U1702.5 (VCC); also elsewhere on the board
VMAIN: C1403.1, C1603.1, C1703.1, R1402.1, R1602.1, R1702.1, U1601.4 (R), U1601.10 (R), U1601.14 (VCC); also elsewhere on the board
~MCU_RSTn: U1402.3, U1603.3, U1702.3; also elsewhere on the board

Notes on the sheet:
Ra=15k, Cs=1uF -> T_max = 15ms
(Alt. 4k7 / 6k8 : 4.90V)
Latching a '1' on rising-edge of "PWM_ENABLE". Flag is cleared on ~{PULSE_ERR}, i.e. after a PWM-stuck-high timeout. This is assumed to gate the PWM-pulse input to off, which will clear the ~{PULSE_ERR} from the 555, which will allow the D-flipflop to be re-enabled by a subsequent toggling 1->0->1 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
12V PWM pulse-train for Heater

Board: 4 copper layers, 487 parts (133 on the bottom side), 299 nets, no tracks yet.

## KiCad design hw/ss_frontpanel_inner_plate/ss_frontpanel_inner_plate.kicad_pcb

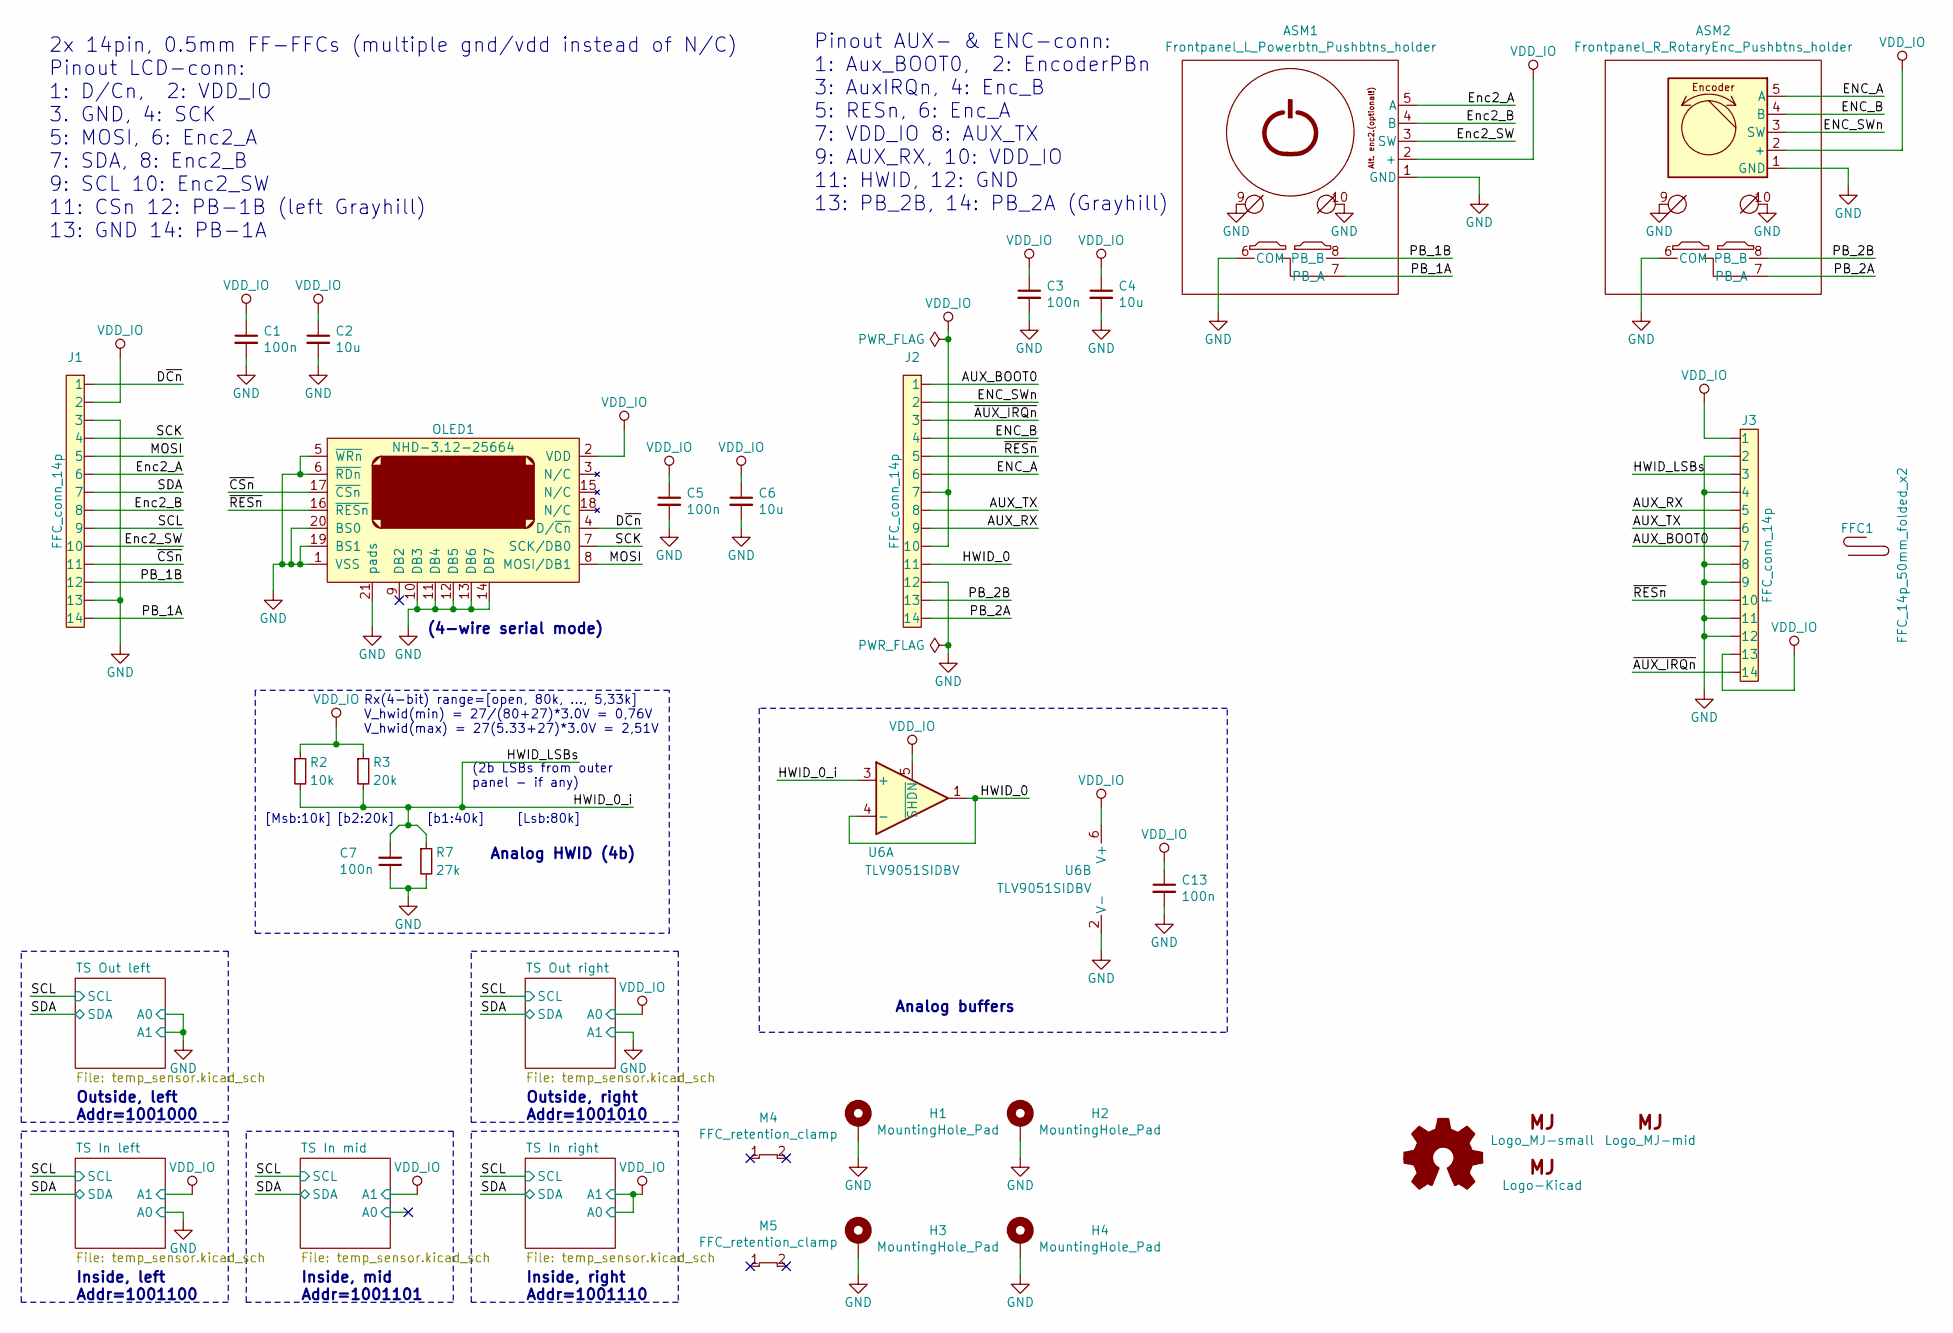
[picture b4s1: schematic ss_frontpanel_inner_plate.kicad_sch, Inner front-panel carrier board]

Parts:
ASM1: Frontpanel_L_Powerbtn_Pushbtns_holder
ASM2: Frontpanel_R_RotaryEnc_Pushbtns_holder; Frontpanel_R_RotaryEnc_Pushbtns_holder-one_M3_removed
C1, C3, C5, C7, C13: 100n; C_0603_1608Metric
C2, C4, C6: 10u; C_0603_1608Metric
FFC1: FFC_14p_50mm_folded_x2; FFC_mech_14p_50mm_folded_x2
H1, H2, H3, H4: MountingHole_Pad; MountingHole_3-6mm_pth
J1, J2: FFC_conn_14p; FPC_14p_05mm-Universal
J3: FFC_conn_14p; FPC_14p_05mm-WE_687114182122
Logo3: Logo_MJ-small; MJ_Mini
Logo4: Logo_MJ-mid; MJ_10.3x12.7
Logo5: Logo-Kicad; KiCad-Logo2_5mm_SilkScreen
Logo_OSHW1: Logo_Open_Hardware_Small; OSHW-Logo_5.7x6mm_SilkScreen
M4, M5: FFC_retention_clamp; FFC_retention_clamp_14pin_7_5mm
OLED1: NHD-3.12-25664; NHD3_12-Flush_without_bridge_cutouts
R2: 10k; R_0603_1608Metric
R3: 20k; R_0603_1608Metric
R7: 27k; R_0603_1608Metric
U6: TLV9051SIDBV; SOT-23-6_Handsoldering

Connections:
/AUX_BOOT0: J2.1, J3.7
/AUX_RX: J2.9, J3.5
/AUX_TX: J2.8, J3.6
/D~Cn: J1.1, OLED1.4 (D/~Cn)
/ENC_A: ASM2.5 (A), J2.6
/ENC_B: ASM2.4 (B), J2.4
/ENC_SWn: ASM2.3 (SW), J2.2
/Enc2_A: ASM1.5 (A), J1.6
/Enc2_B: ASM1.4 (B), J1.8
/Enc2_SW: ASM1.3 (SW), J1.10
/HWID_0: J2.11, U6.1, U6.4 (-)
/HWID_0_i: C7.2, J3.3, R2.2, R3.2, R7.1, U6.3 (+)
/MOSI: J1.5, OLED1.8 (MOSI/DB1)
/PB_1A: ASM1.7 (PB_A), J1.14
/PB_1B: ASM1.8 (PB_B), J1.12
/PB_2A: ASM2.7 (PB_A), J2.14
/PB_2B: ASM2.8 (PB_B), J2.13
/SCK: J1.4, OLED1.7 (SCK/DB0)
/SCL: J1.9; also elsewhere on the board
/SDA: J1.7; also elsewhere on the board
/~AUX_IRQn: J2.3, J3.14
/~CSn: J1.11, OLED1.17 (~CSn)
/~RESn: J2.5, J3.10, OLED1.16 (~RESn)
GND: ASM1.1 (GND), ASM1.6 (COM), ASM1.9, ASM1.10, ASM2.1 (GND), ASM2.6 (COM), ASM2.9, ASM2.10, C1.2, C2.2, C3.2, C4.2, C5.2, C6.2, C7.1, C13.2, H1.1, H2.1, H3.1, H4.1, J1.3, J1.13, J2.12, J3.2, J3.4, J3.8, J3.9, J3.11, J3.12, OLED1.1 (VSS), OLED1.5 (~WRn), OLED1.6 (~RDn), OLED1.10 (DB3), OLED1.11 (DB4), OLED1.12 (DB5), OLED1.13 (DB6), OLED1.14 (DB7), OLED1.19 (BS1), OLED1.20 (BS0), OLED1.21 (pads), R7.2, U6.2 (V-); also elsewhere on the board
VDD_IO: ASM1.2 (+), ASM2.2 (+), C1.1, C2.1, C3.1, C4.1, C5.1, C6.1, C13.1, J1.2, J2.7, J2.10, J3.1, J3.13, OLED1.2 (VDD), R2.1, R3.1, U6.5 (~SHDN), U6.6 (V+); also elsewhere on the board

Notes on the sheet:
2x 14pin, 0.5mm FF-FFCs (multiple gnd/vdd instead of N/C) Pinout LCD-conn: 1: D/Cn, 2: VDD_IO 3. GND, 4: SCK 5: MOSI, 6: Enc2_A 7: SDA, 8: Enc2_B 9: SCL 10: Enc2_SW 11: CSn 12: PB-1B (left Grayhill) 13: GND 14: PB-1A
Rx(4-bit) range=[open, 80k, ..., 5,33k] V_hwid(min) = 27/(80+27)*3.0V = 0,76V V_hwid(max) = 27(5.33+27)*3.0V = 2,51V
Inside, right Addr=1001110
Outside, left Addr=1001000
[b1:40k]
[Msb:10k]
Inside, left Addr=1001100
Analog buffers
Inside, mid Addr=1001101
Pinout AUX- & ENC-conn: 1: Aux_BOOT0, 2: EncoderPBn 3: AuxIRQn, 4: Enc_B 5: RESn, 6: Enc_A 7: VDD_IO 8: AUX_TX 9: AUX_RX, 10: VDD_IO 11: HWID, 12: GND 13: PB_2B, 14: PB_2A (Grayhill)
[Lsb:80k]
(2b LSBs from outer panel - if any)
Outside, right Addr=1001010
[b2:20k]
Analog HWID (4b)
(4-wire serial mode)
